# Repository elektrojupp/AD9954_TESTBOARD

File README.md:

# AD9954_TESTBOARD
Testboard for AD9954 controlled by a STM32L4. Available interfaces: SWD, CAN, USB and GUI

# Hardware
Hardware folder contains PCB in as Kicad project.
All used components/footprints/3D models in project specific libary, so it should be possible to open without problems.

# Software
Software folder contains a STM32CubeIDE project. 
For compilation it might be necessary to have the STM32L4 support package installed.
All interfaces are accessible via software:
AD9954 can run in single tone mode,
USB runs as loopserver, CAN interface initiates (no further testing).
GUI menue structure is a bit blown up but flexible. 
STM32L4 runs FREERTOS RTO. Every interface has its own task. 
Communication over queues and semaphores, between different tasks,
so its possible to implement communication over USB/CAN to AD9954.
When a button is pressed during RESET, a snake game appears. 
Speacial feature of the snake game is to store the highscore in flash (simple eeprom emulation).

# Frontview PCB 
More Pictures in Picture folder

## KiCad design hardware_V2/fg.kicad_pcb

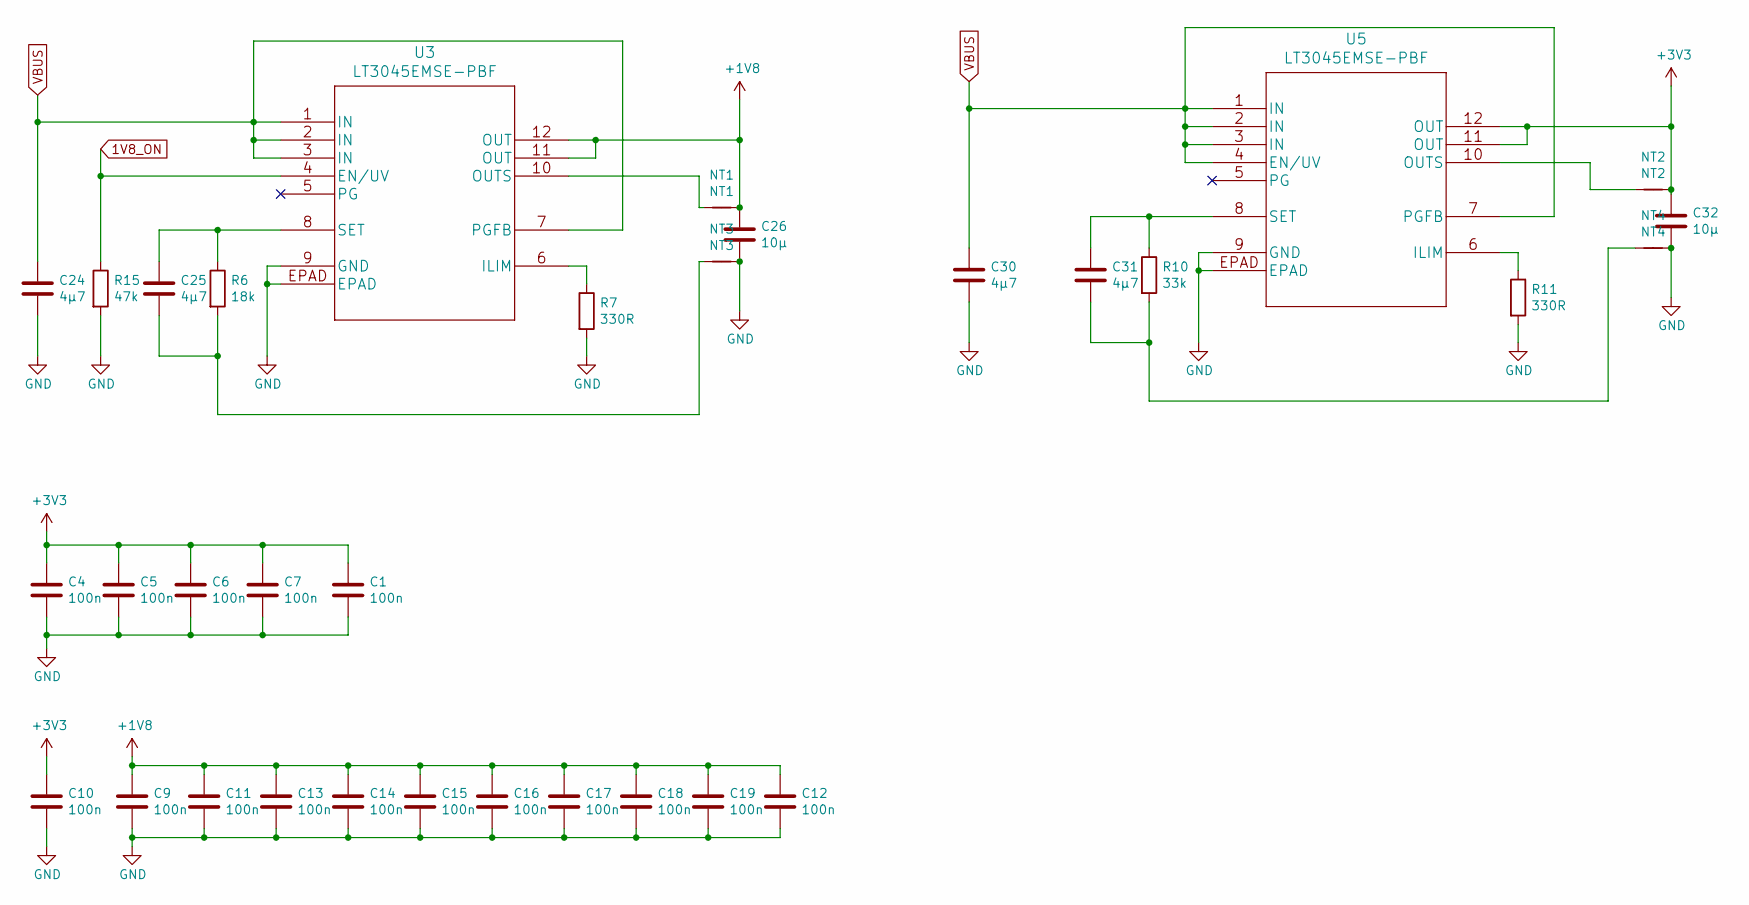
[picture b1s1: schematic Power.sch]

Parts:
C1, C4, C5, C6, C7, C9, C10, C11, C12, C13, C14, C15, C16, C17, C18, C19: 100n; C_0402_1005Metric
C24, C25, C30, C31: 4µ7; C_1206_3216Metric
C26, C32: 10µ; C_1206_3216Metric
NT1: NT1; NetTie-2_SMD_Pad0.5mm
NT2: NT2; NetTie-2_SMD_Pad0.5mm
NT3: NT3; NetTie-2_SMD_Pad1.0mm
NT4: NT4; NetTie-2_SMD_Pad1.0mm
R6: 18k; R_0603_1608Metric
R7, R11: 330R; R_0603_1608Metric
R10: 33k; R_0603_1608Metric
R15: 47k; R_0603_1608Metric
U3, U5: LT3045EMSE-PBF

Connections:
1V8_ON: R15.1, U3.4 (EN/UV); also elsewhere on the board
+1V8: C9.1, C11.1, C12.1, C13.1, C14.1, C15.1, C16.1, C17.1, C18.1, C19.1, C26.1, NT1.2, U3.11 (OUT), U3.12 (OUT); also elsewhere on the board
+3V3: C1.1, C4.1, C5.1, C6.1, C7.1, C10.1, C32.1, NT2.2, U5.11 (OUT), U5.12 (OUT); also elsewhere on the board
GND: C1.2, C4.2, C5.2, C6.2, C7.2, C9.2, C10.2, C11.2, C12.2, C13.2, C14.2, C15.2, C16.2, C17.2, C18.2, C19.2, C24.2, C26.2, C30.2, C32.2, NT3.2, NT4.2, R7.2, R11.2, R15.2, U3.9 (GND), U3.EPAD, U5.9 (GND), U5.EPAD; also elsewhere on the board
unnamed: C25.1, R6.1, U3.8 (SET)
unnamed: C25.2, NT3.1, R6.2
unnamed: C31.1, R10.1, U5.8 (SET)
unnamed: C31.2, NT4.1, R10.2
unnamed: NT1.1, U3.10 (OUTS)
unnamed: NT2.1, U5.10 (OUTS)
unnamed: R7.1, U3.6 (ILIM)
unnamed: R11.1, U5.6 (ILIM)
VBUS: C24.1, C30.1, U3.1 (IN), U3.2 (IN), U3.3 (IN), U3.7 (PGFB), U5.1 (IN), U5.2 (IN), U5.3 (IN), U5.4 (EN/UV), U5.7 (PGFB); also elsewhere on the board

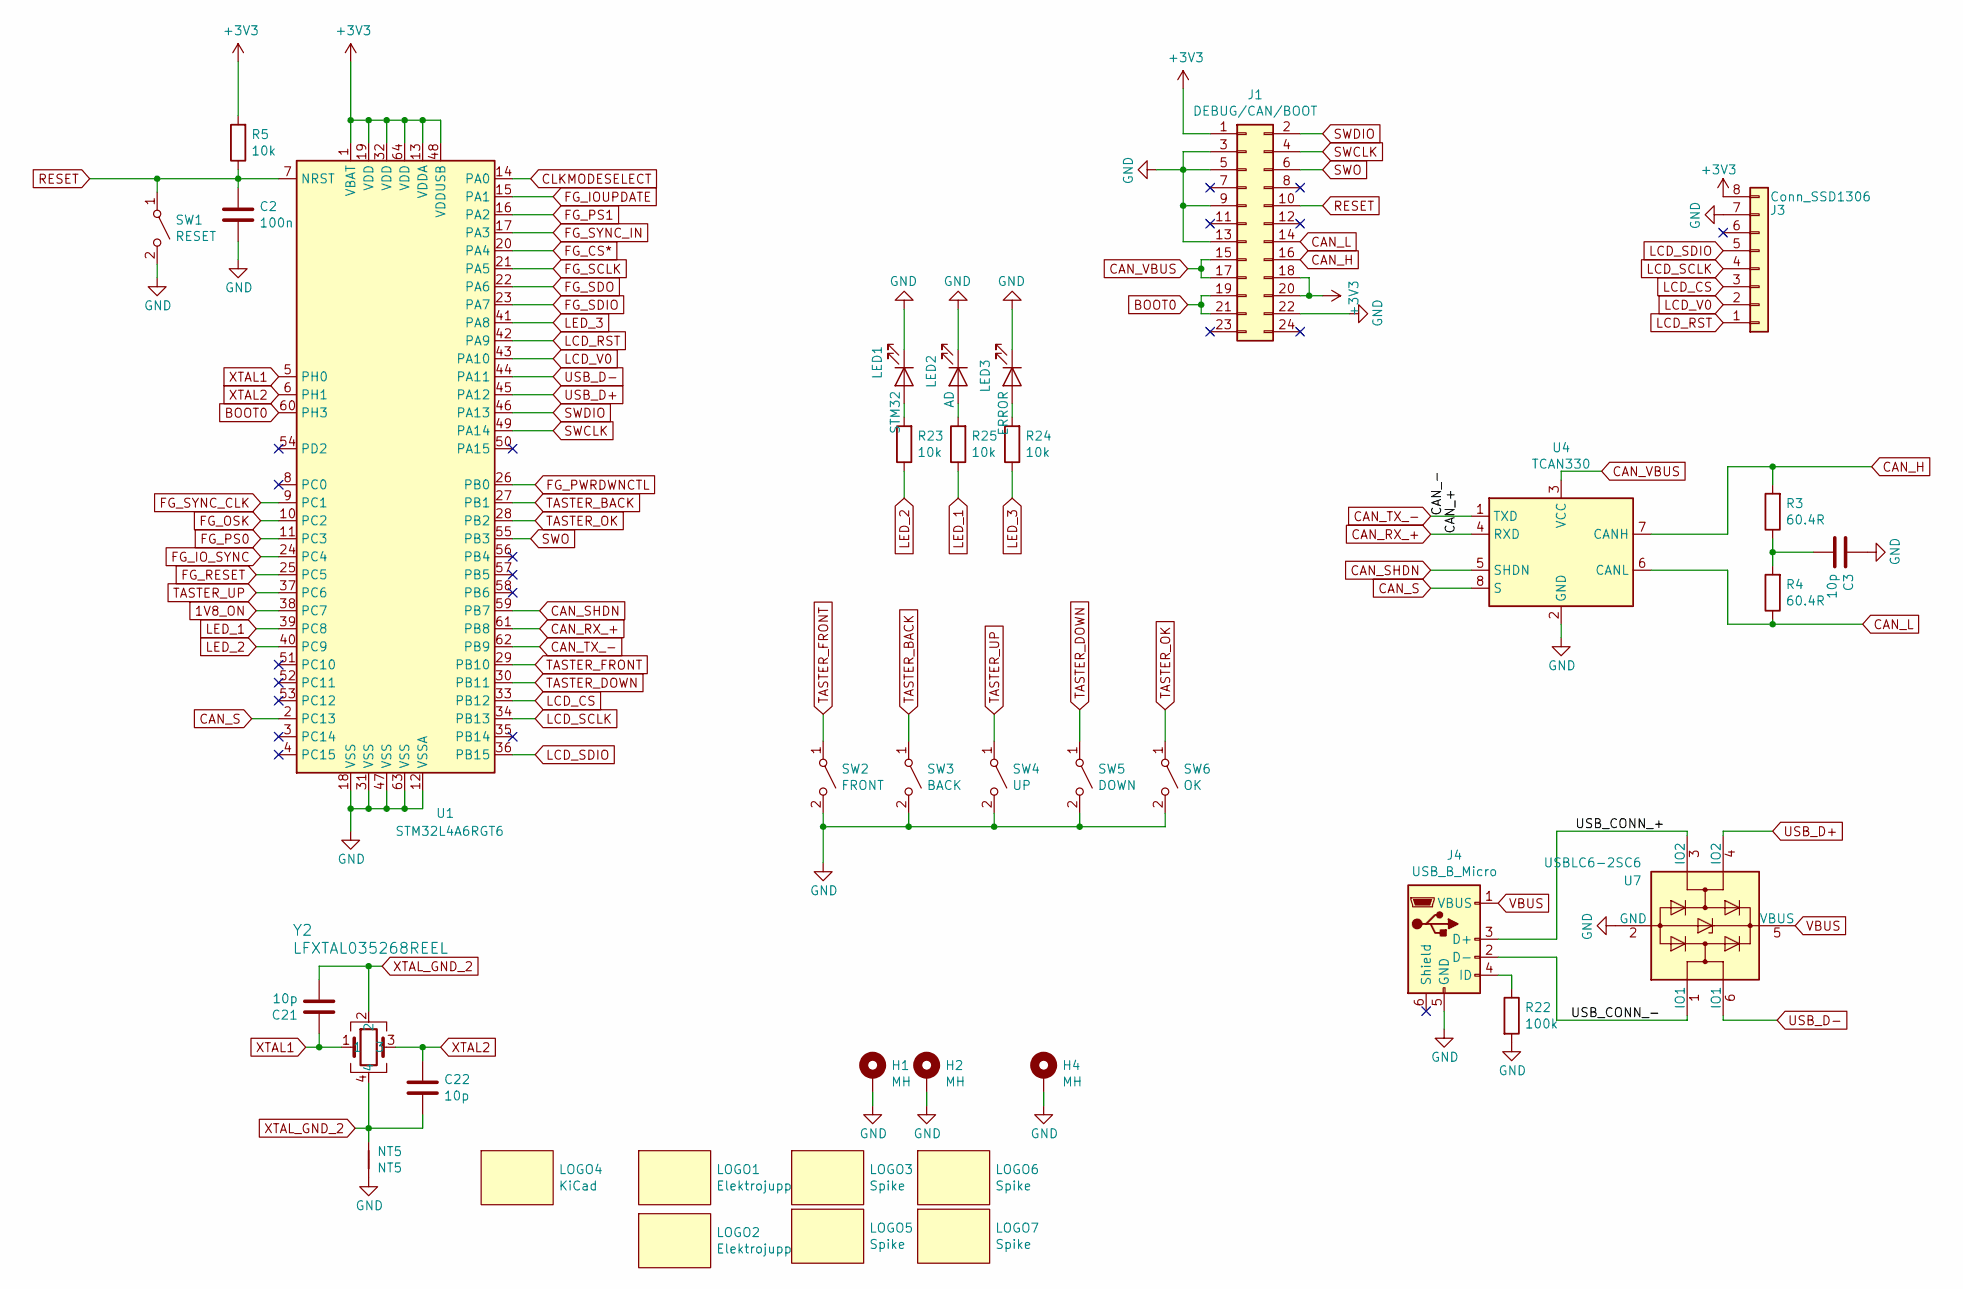
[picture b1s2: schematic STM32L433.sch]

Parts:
C2: 100n; C_0402_1005Metric
C3, C21, C22: 10p; C_0402_1005Metric
H1, H2, H4: MH; MountingHole_2.7mm_M2.5_Pad_Via
J1: DEBUG/CAN/BOOT; PinHeader_2x12_P2.54mm_Vertical
J3: Conn_SSD1306; Adafruit_SSD1306
J4: USB_B_Micro; USB_Micro-B_Wuerth_629105150521
LED1: STM32; LED_D5.0mm
LED2: AD; LED_D5.0mm
LED3: ERROR; LED_D5.0mm
LOGO1, LOGO2: Elektrojupp; Logo_Elektrojupp
LOGO3, LOGO5, LOGO6, LOGO7: Spike
LOGO4: KiCad; KiCad-Logo2_12mm_SilkScreen
NT5: NT5; NetTie-2_SMD_Pad0.5mm
R3, R4: 60.4R; R_1206_3216Metric
R5, R23, R24, R25: 10k; R_0603_1608Metric
R22: 100k; R_0603_1608Metric
SW1: RESET; SW_PUSH_6mm_H5mm
SW2: FRONT; SW_PUSH_6mm_H5mm
SW3: BACK; SW_PUSH_6mm_H5mm
SW4: UP; SW_PUSH_6mm_H5mm
SW5: DOWN; SW_PUSH_6mm_H5mm
SW6: OK; SW_PUSH_6mm_H5mm
U1: STM32L4A6RGT6; LQFP-64_10x10mm_P0.5mm
U4: TCAN330; SOT-23-8
U7: USBLC6-2SC6; SOT-23-6
Y2: LFXTAL035268REEL; CFPX-180

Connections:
1V8_ON: U1.38 (PC7); also elsewhere on the board
+3V3: J1.1, J1.18, J1.20, J3.8, R5.2, U1.1 (VBAT), U1.13 (VDDA), U1.19 (VDD), U1.32 (VDD), U1.48 (VDDUSB), U1.64 (VDD); also elsewhere on the board
/STM32L433/USB_CONN_+: J4.3 (D+), U7.3 (IO2)
/STM32L433/USB_CONN_-: J4.2 (D-), U7.1 (IO1)
BOOT0: J1.19, J1.21, U1.60 (PH3)
CAN_H: J1.16, R3.2, U4.7 (CANH)
CAN_L: J1.14, R4.1, U4.6 (CANL)
CAN_RX_+: U1.61 (PB8), U4.4 (RXD)
CAN_S: U1.2 (PC13), U4.8 (S)
CAN_SHDN: U1.59 (PB7), U4.5 (SHDN)
CAN_TX_-: U1.62 (PB9), U4.1 (TXD)
CAN_VBUS: J1.15, J1.17, U4.3 (VCC)
CLKMODESELECT: U1.14 (PA0); also elsewhere on the board
FG_CS*: U1.20 (PA4); also elsewhere on the board
FG_IOUPDATE: U1.15 (PA1); also elsewhere on the board
FG_IO_SYNC: U1.24 (PC4); also elsewhere on the board
FG_OSK: U1.10 (PC2); also elsewhere on the board
FG_PS0: U1.11 (PC3); also elsewhere on the board
FG_PS1: U1.16 (PA2); also elsewhere on the board
FG_PWRDWNCTL: U1.26 (PB0); also elsewhere on the board
FG_RESET: U1.25 (PC5); also elsewhere on the board
FG_SCLK: U1.21 (PA5); also elsewhere on the board
FG_SDIO: U1.23 (PA7); also elsewhere on the board
FG_SDO: U1.22 (PA6); also elsewhere on the board
FG_SYNC_CLK: U1.9 (PC1); also elsewhere on the board
FG_SYNC_IN: U1.17 (PA3); also elsewhere on the board
GND: C2.2, C3.1, H1.1, H2.1, H4.1, J1.3, J1.5, J1.9, J1.13, J1.22, J3.7, J4.5 (GND), LED1.1 (K), LED2.1 (K), LED3.1 (K), NT5.1, R22.2, SW1.2 (B), SW2.2 (B), SW3.2 (B), SW4.2 (B), SW5.2 (B), SW6.2 (B), U1.12 (VSSA), U1.18 (VSS), U1.31 (VSS), U1.47 (VSS), U1.63 (VSS), U4.2 (GND), U7.2 (GND); also elsewhere on the board
LCD_CS: J3.3, U1.33 (PB12)
LCD_RST: J3.1, U1.42 (PA9)
LCD_SCLK: J3.4, U1.34 (PB13)
LCD_SDIO: J3.5, U1.36 (PB15)
LCD_V0: J3.2, U1.43 (PA10)
LED_1: R25.1, U1.39 (PC8)
LED_2: R23.1, U1.40 (PC9)
LED_3: R24.1, U1.41 (PA8)
unnamed: C3.2, R3.1, R4.2
unnamed: J4.4 (ID), R22.1
unnamed: LED1.2 (A), R23.2
unnamed: LED2.2 (A), R25.2
unnamed: LED3.2 (A), R24.2
RESET: C2.1, J1.10, R5.1, SW1.1 (A), U1.7 (NRST)
SWCLK: J1.4, U1.49 (PA14)
SWDIO: J1.2, U1.46 (PA13)
SWO: J1.6, U1.55 (PB3)
TASTER_BACK: SW3.1 (A), U1.27 (PB1)
TASTER_DOWN: SW5.1 (A), U1.30 (PB11)
TASTER_FRONT: SW2.1 (A), U1.29 (PB10)
TASTER_OK: SW6.1 (A), U1.28 (PB2)
TASTER_UP: SW4.1 (A), U1.37 (PC6)
USB_D+: U1.45 (PA12), U7.4 (IO2)
USB_D-: U1.44 (PA11), U7.6 (IO1)
VBUS: J4.1 (VBUS), U7.5 (VBUS); also elsewhere on the board
XTAL1: C21.1, U1.5 (PH0), Y2.1
XTAL2: C22.1, U1.6 (PH1), Y2.3
XTAL_GND_2: C21.2, C22.2, NT5.2, Y2.2, Y2.4

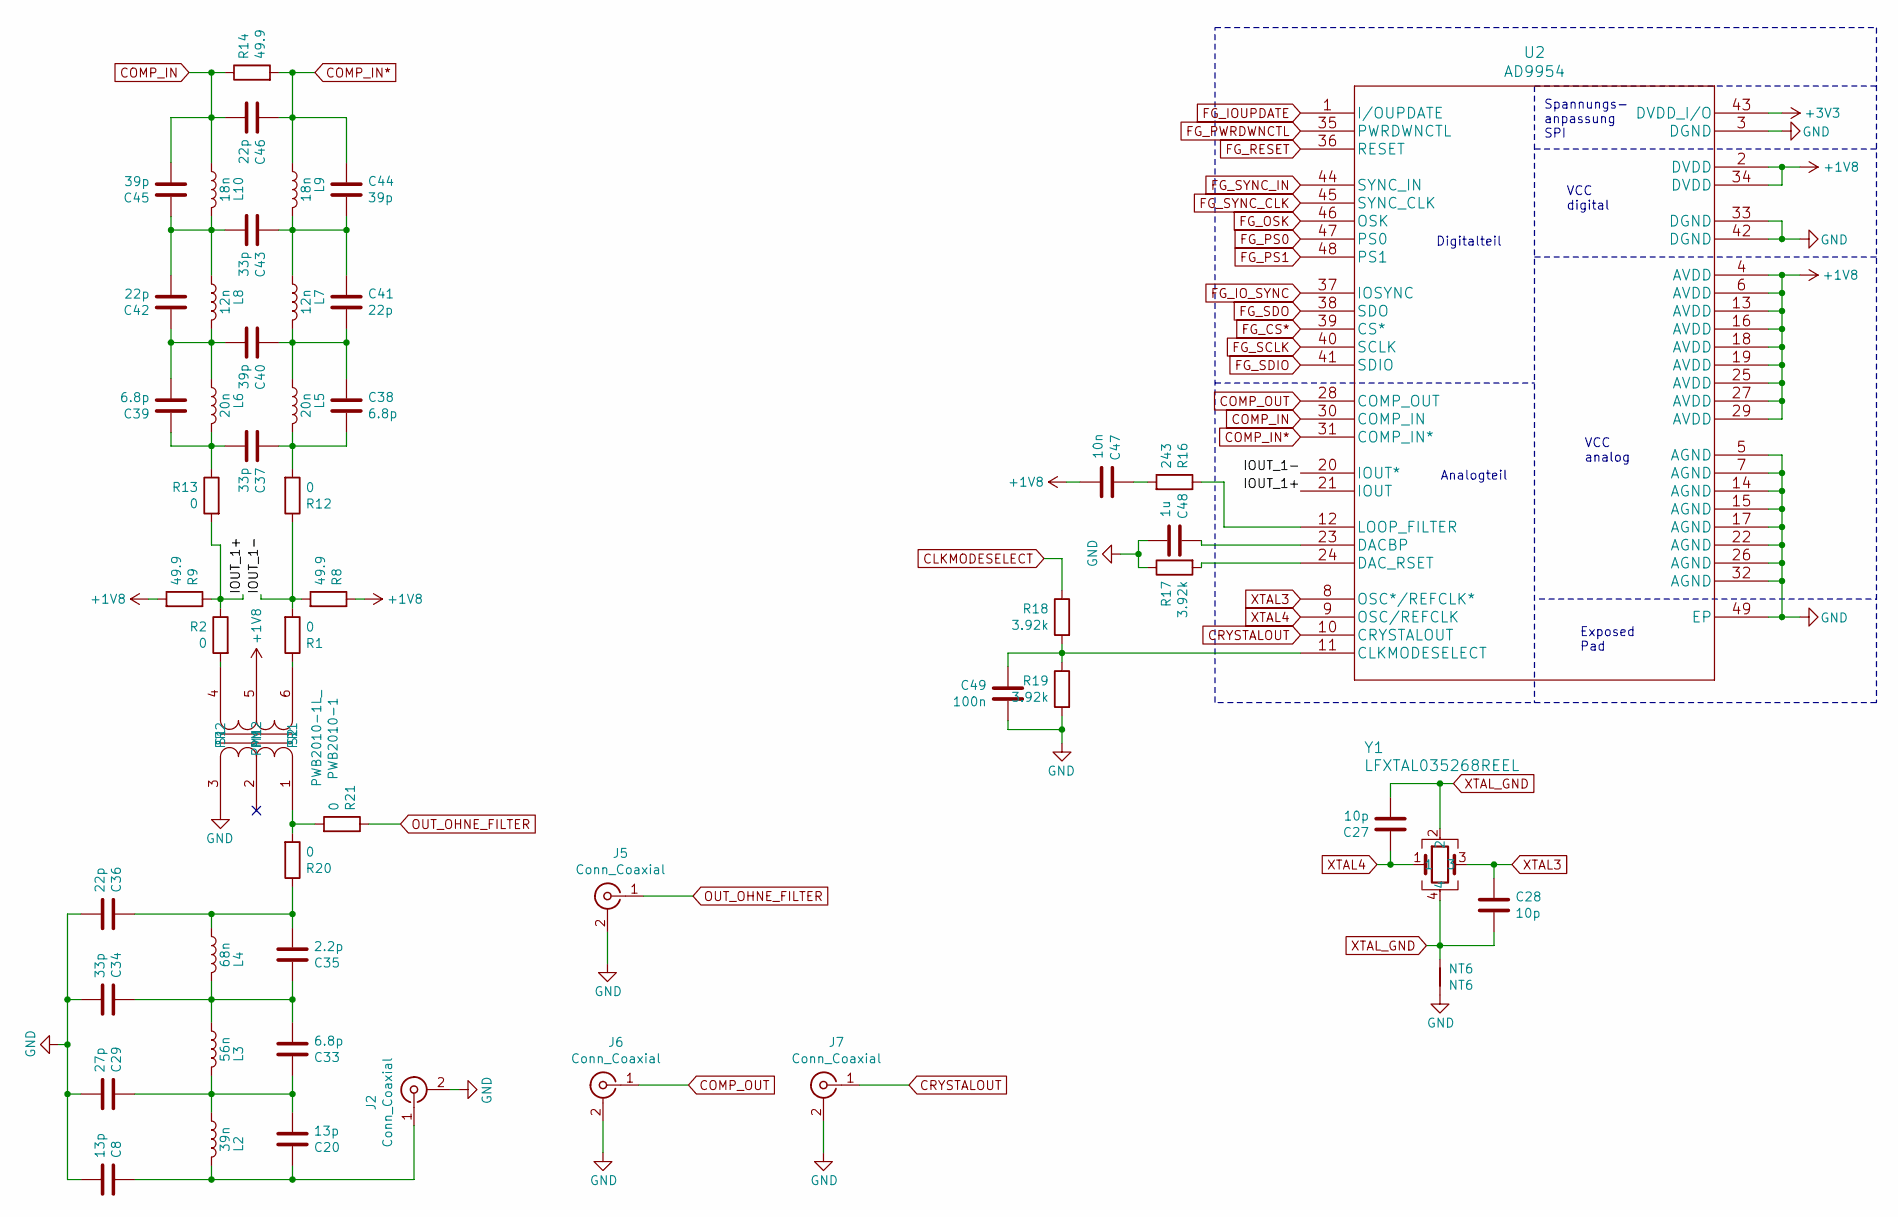
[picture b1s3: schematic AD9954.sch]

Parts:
C8, C20: 13p; C_0402_1005Metric
C27, C28: 10p; C_0402_1005Metric
C29: 27p; C_0402_1005Metric
C33, C38, C39: 6.8p; C_0402_1005Metric
C34, C37, C43: 33p; C_0402_1005Metric
C35: 2.2p; C_0402_1005Metric
C36, C41, C42, C46: 22p; C_0402_1005Metric
C40, C44, C45: 39p; C_0402_1005Metric
C47: 10n; C_0402_1005Metric
C48: 1u; C_1206_3216Metric
C49: 100n; C_0402_1005Metric
J2, J5, J6, J7: Conn_Coaxial; SMA_Amphenol_132291_Vertical
L2: 39n; 1008HQ39NXGLB
L3: 56n; 1008HQ39NXGLB
L4: 68n; 1008HQ39NXGLB
L5, L6: 20n; L_0603_1608Metric
L7, L8: 12n; L_0603_1608Metric
L9, L10: 18n; L_0603_1608Metric
NT6: NT6; NetTie-2_SMD_Pad0.5mm
PWB2010-1: PWB2010-1L_; Transformer_NF_ETAL
R1, R2, R12, R13, R20, R21: 0; R_0603_1608Metric
R8, R9, R14: 49.9; R_1206_3216Metric
R16: 243; R_1206_3216Metric
R17, R18, R19: 3.92k; R_0603_1608Metric
U2: AD9954
Y1: LFXTAL035268REEL; CFPX-180

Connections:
+1V8: C47.2, PWB2010-1.5 (PM1), R8.1, R9.2, U2.2 (DVDD), U2.4 (AVDD), U2.6 (AVDD), U2.13 (AVDD), U2.16 (AVDD), U2.18 (AVDD), U2.19 (AVDD), U2.25 (AVDD), U2.27 (AVDD), U2.29 (AVDD), U2.34 (DVDD); also elsewhere on the board
+3V3: U2.43 (DVDD_I/O); also elsewhere on the board
/AD9954/IOUT_1+: R2.1, R9.1, R13.2, U2.21 (IOUT)
/AD9954/IOUT_1-: R1.2, R8.2, R12.1, U2.20 (IOUT*)
CLKMODESELECT: R18.1; also elsewhere on the board
COMP_IN: C45.2, C46.2, L10.1, R14.1, U2.30 (COMP_IN)
COMP_IN*: C44.1, C46.1, L9.1, R14.2, U2.31 (COMP_IN*)
COMP_OUT: J6.1 (In), U2.28 (COMP_OUT)
CRYSTALOUT: J7.1 (In), U2.10 (CRYSTALOUT)
FG_CS*: U2.39 (CS*); also elsewhere on the board
FG_IOUPDATE: U2.1 (I/OUPDATE); also elsewhere on the board
FG_IO_SYNC: U2.37 (IOSYNC); also elsewhere on the board
FG_OSK: U2.46 (OSK); also elsewhere on the board
FG_PS0: U2.47 (PS0); also elsewhere on the board
FG_PS1: U2.48 (PS1); also elsewhere on the board
FG_PWRDWNCTL: U2.35 (PWRDWNCTL); also elsewhere on the board
FG_RESET: U2.36 (RESET); also elsewhere on the board
FG_SCLK: U2.40 (SCLK); also elsewhere on the board
FG_SDIO: U2.41 (SDIO); also elsewhere on the board
FG_SDO: U2.38 (SDO); also elsewhere on the board
FG_SYNC_CLK: U2.45 (SYNC_CLK); also elsewhere on the board
FG_SYNC_IN: U2.44 (SYNC_IN); also elsewhere on the board
GND: C8.2, C29.2, C34.2, C36.2, C48.2, C49.2, J2.2 (Ext), J5.2 (Ext), J6.2 (Ext), J7.2 (Ext), NT6.1, PWB2010-1.3 (PR2), R17.1, R19.2, U2.3 (DGND), U2.5 (AGND), U2.7 (AGND), U2.14 (AGND), U2.15 (AGND), U2.17 (AGND), U2.22 (AGND), U2.26 (AGND), U2.32 (AGND), U2.33 (DGND), U2.42 (DGND), U2.49 (EP); also elsewhere on the board
unnamed: C8.1, C20.1, J2.1 (In), L2.1
unnamed: C20.2, C29.1, C33.1, L2.2, L3.1
unnamed: C33.2, C34.1, C35.1, L3.2, L4.1
unnamed: C35.2, C36.1, L4.2, R20.1
unnamed: C37.1, C38.2, L5.2, R12.2
unnamed: C37.2, C39.1, L6.2, R13.1
unnamed: C38.1, C40.1, C41.2, L5.1, L7.2
unnamed: C39.2, C40.2, C42.1, L6.1, L8.2
unnamed: C41.1, C43.1, C44.2, L7.1, L9.2
unnamed: C42.2, C43.2, C45.1, L8.1, L10.2
unnamed: C47.1, R16.2
unnamed: C48.1, U2.23 (DACBP)
unnamed: C49.1, R18.2, R19.1, U2.11 (CLKMODESELECT)
unnamed: PWB2010-1.1 (PR1), R20.2, R21.2
unnamed: PWB2010-1.4 (S1), R2.2
unnamed: PWB2010-1.6 (S2), R1.1
unnamed: R16.1, U2.12 (LOOP_FILTER)
unnamed: R17.2, U2.24 (DAC_RSET)
OUT_OHNE_FILTER: J5.1 (In), R21.1
XTAL3: C28.1, U2.8 (OSC*/REFCLK*), Y1.3
XTAL4: C27.1, U2.9 (OSC/REFCLK), Y1.1
XTAL_GND: C27.2, C28.2, NT6.2, Y1.2, Y1.4

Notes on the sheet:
Analogteil
Digitalteil
Spannungs- anpassung SPI
VCC digital
VCC analog
Exposed Pad

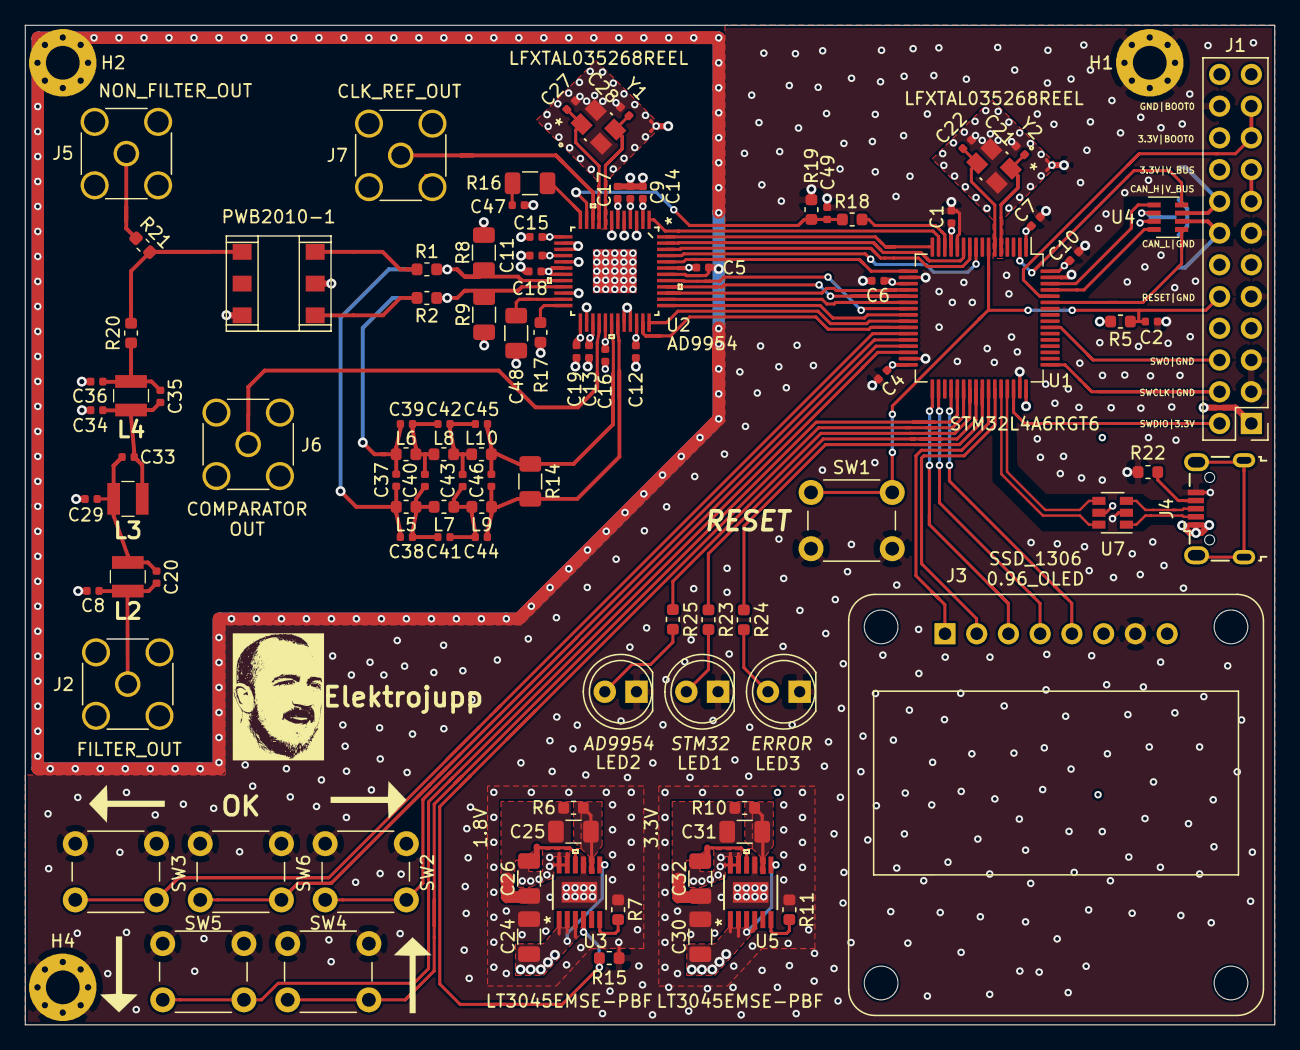
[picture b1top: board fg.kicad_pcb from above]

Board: 4 copper layers, 100.0 x 80.0 mm, 123 parts (0 on the bottom side), 92 nets.

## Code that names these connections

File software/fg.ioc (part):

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Mcu.Name=STM32L4A6RGTx
Mcu.Package=LQFP64
Mcu.UserName=STM32L4A6RGTx
PA0.GPIOParameters=GPIO_Label
PA0.GPIO_Label=FG_CLKMODESELECT
PA0.Signal=GPIO_Output
PA1.GPIOParameters=GPIO_Label
PA1.GPIO_Label=FG_IOUPDATE
PA1.Signal=GPIO_Output
PA10.GPIOParameters=GPIO_Label
PA10.GPIO_Label=LCD_V0
PA10.Signal=GPIO_Output
PA11.Mode=Device_Only
PA11.Signal=USB_OTG_FS_DM
PA12.Mode=Device_Only
PA12.Signal=USB_OTG_FS_DP
PA13\ (JTMS/SWDIO).Mode=Serial_Wire
PA13\ (JTMS/SWDIO).Signal=SYS_JTMS-SWDIO
PA14\ (JTCK/SWCLK).Mode=Serial_Wire
PA14\ (JTCK/SWCLK).Signal=SYS_JTCK-SWCLK
PA2.GPIOParameters=GPIO_Label
PA2.GPIO_Label=FG_PS1
PA2.Signal=GPIO_Output
PA3.GPIOParameters=GPIO_Label
PA3.GPIO_Label=FG_SYNC_IN
PA3.Signal=GPIO_Output
PA4.GPIOParameters=GPIO_Label
PA4.GPIO_Label=FG_SPI_NSS
PA4.Mode=NSS_Signal_Hard_Output
PA4.Signal=SPI1_NSS
PA5.GPIOParameters=GPIO_Label
PA5.GPIO_Label=FG_SPI_SCLK
PA5.Mode=Full_Duplex_Master
PA5.Signal=SPI1_SCK
PA6.Mode=Full_Duplex_Master
PA6.Signal=SPI1_MISO
PA7.GPIOParameters=GPIO_Label
PA7.GPIO_Label=FG_SPI_MOSI
PA7.Mode=Full_Duplex_Master
PA7.Signal=SPI1_MOSI
PA8.GPIOParameters=GPIO_Label
PA8.GPIO_Label=LED_ERROR
PA8.Signal=GPIO_Output
PA9.GPIOParameters=GPIO_Label
PA9.GPIO_Label=LCD_RST
PA9.Signal=GPIO_Output
PB0.GPIOParameters=GPIO_Label
PB0.GPIO_Label=FG_PWRDNCTL
PB0.Signal=GPIO_Output
PB1.GPIOParameters=GPIO_PuPd,GPIO_Label
PB1.GPIO_Label=TASTER_BACK
PB1.GPIO_PuPd=GPIO_PULLUP
PB1.Signal=GPIO_Input
PB10.GPIOParameters=GPIO_PuPd,GPIO_Label
PB10.GPIO_Label=TASTER_FRONT
PB10.GPIO_PuPd=GPIO_PULLUP
PB10.Signal=GPIO_Input
PB11.GPIOParameters=GPIO_PuPd,GPIO_Label
PB11.GPIO_Label=TASTER_DOWN
PB11.GPIO_PuPd=GPIO_PULLUP
PB11.Signal=GPIO_Input
PB12.GPIOParameters=GPIO_Label
PB12.GPIO_Label=LCD_SOFTWARE_NSS
PB12.Signal=GPIO_Output
PB13.GPIOParameters=GPIO_Label
PB13.GPIO_Label=LCD_SPI_SCLK
PB13.Mode=TX_Only_Simplex_Unidirect_Master
PB13.Signal=SPI2_SCK
PB15.GPIOParameters=GPIO_Label
PB15.GPIO_Label=LCD_SPI_MOSI
PB15.Mode=TX_Only_Simplex_Unidirect_Master
PB15.Signal=SPI2_MOSI
PB2.GPIOParameters=GPIO_PuPd,GPIO_Label
PB2.GPIO_Label=TASTER_OK
PB2.GPIO_PuPd=GPIO_PULLUP
PB2.Signal=GPIO_Input
PB7.GPIOParameters=GPIO_Label
PB7.GPIO_Label=CAN_SHDN
PB7.Signal=GPIO_Output
PB8.Mode=CAN_Activate
PB8.Signal=CAN1_RX
PB9.Mode=CAN_Activate
PB9.Signal=CAN1_TX
PC1.GPIOParameters=GPIO_Label
PC1.GPIO_Label=FG_SYNC_CLK
PC1.Signal=GPIO_Input
PC13.GPIOParameters=GPIO_Label
PC13.GPIO_Label=CAN_S
PC13.Signal=GPIO_Output
PC2.GPIOParameters=GPIO_Label
PC2.GPIO_Label=FG_OSK
PC2.Signal=GPIO_Output
PC3.GPIOParameters=GPIO_Label
PC3.GPIO_Label=FG_PSO
PC3.Signal=GPIO_Output
PC4.GPIOParameters=GPIO_Label
PC4.GPIO_Label=FG_IO_SYNC
PC4.Signal=GPIO_Output
PC5.GPIOParameters=GPIO_Label
PC5.GPIO_Label=FG_RESET
PC5.Signal=GPIO_Output
PC6.GPIOParameters=GPIO_PuPd,GPIO_Label
PC6.GPIO_Label=TASTER_UP
PC6.GPIO_PuPd=GPIO_PULLUP
PC6.Signal=GPIO_Input
PC7.GPIOParameters=GPIO_Label
PC7.GPIO_Label=SET_1V8
PC7.Signal=GPIO_Output
PC8.GPIOParameters=GPIO_Label
PC8.GPIO_Label=LED_AD9954
PC8.Signal=GPIO_Output
PC9.GPIOParameters=GPIO_Label
PC9.GPIO_Label=LED_STM32
PC9.Signal=GPIO_Output
PH0-OSC_IN\ (PH0).Mode=HSE-External-Clock-Source
PH0-OSC_IN\ (PH0).Signal=RCC_OSC_IN
RCC.HSE_VALUE=8000000
RCC.SYSCLKFreq_VALUE=80000000
RCC.SYSCLKSource=RCC_SYSCLKSOURCE_PLLCLK
board=custom

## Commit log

2021-09-11 Hardware files in KiCad project
2021-09-11 test
2021-09-11 Kicad project files
2021-09-11 create directory
2021-09-11 software files STM32CUBE IDE project
2021-09-11 testfile
2021-09-11 add software files
2021-09-14 add files
2021-09-14 add pictures from PCB and menue structure

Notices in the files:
parts and their libraries:
Copyright 2016 Accelerated Designs. All rights reserved.
